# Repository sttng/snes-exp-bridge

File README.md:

# snes-exp-bridge
This project is intended to create a bridge board interface to the SNES expansion port broken out to DB-25 and 3.5mm barrel audio. The expansion port requires a costly proprietary connector from SAMTEC MEC2-30-01-L-DV or MEC2-50-01-L-TH1-WT or MEC2-50-01-L-DV. Some details also here: https://www.qwertymodo.com/hardware-projects/snes/snes-expansion-port-connector

The idea is instead of creating projects which source this connector, all downstream projects can now instead mate with the DB-25 connector which is cheaper and easier for interfacing. There are no active electrical components for this board. This repo contains altium design files and also newer KiCad files of the schematic/layout, photos and pdf docs.

Enjoy!
Evan

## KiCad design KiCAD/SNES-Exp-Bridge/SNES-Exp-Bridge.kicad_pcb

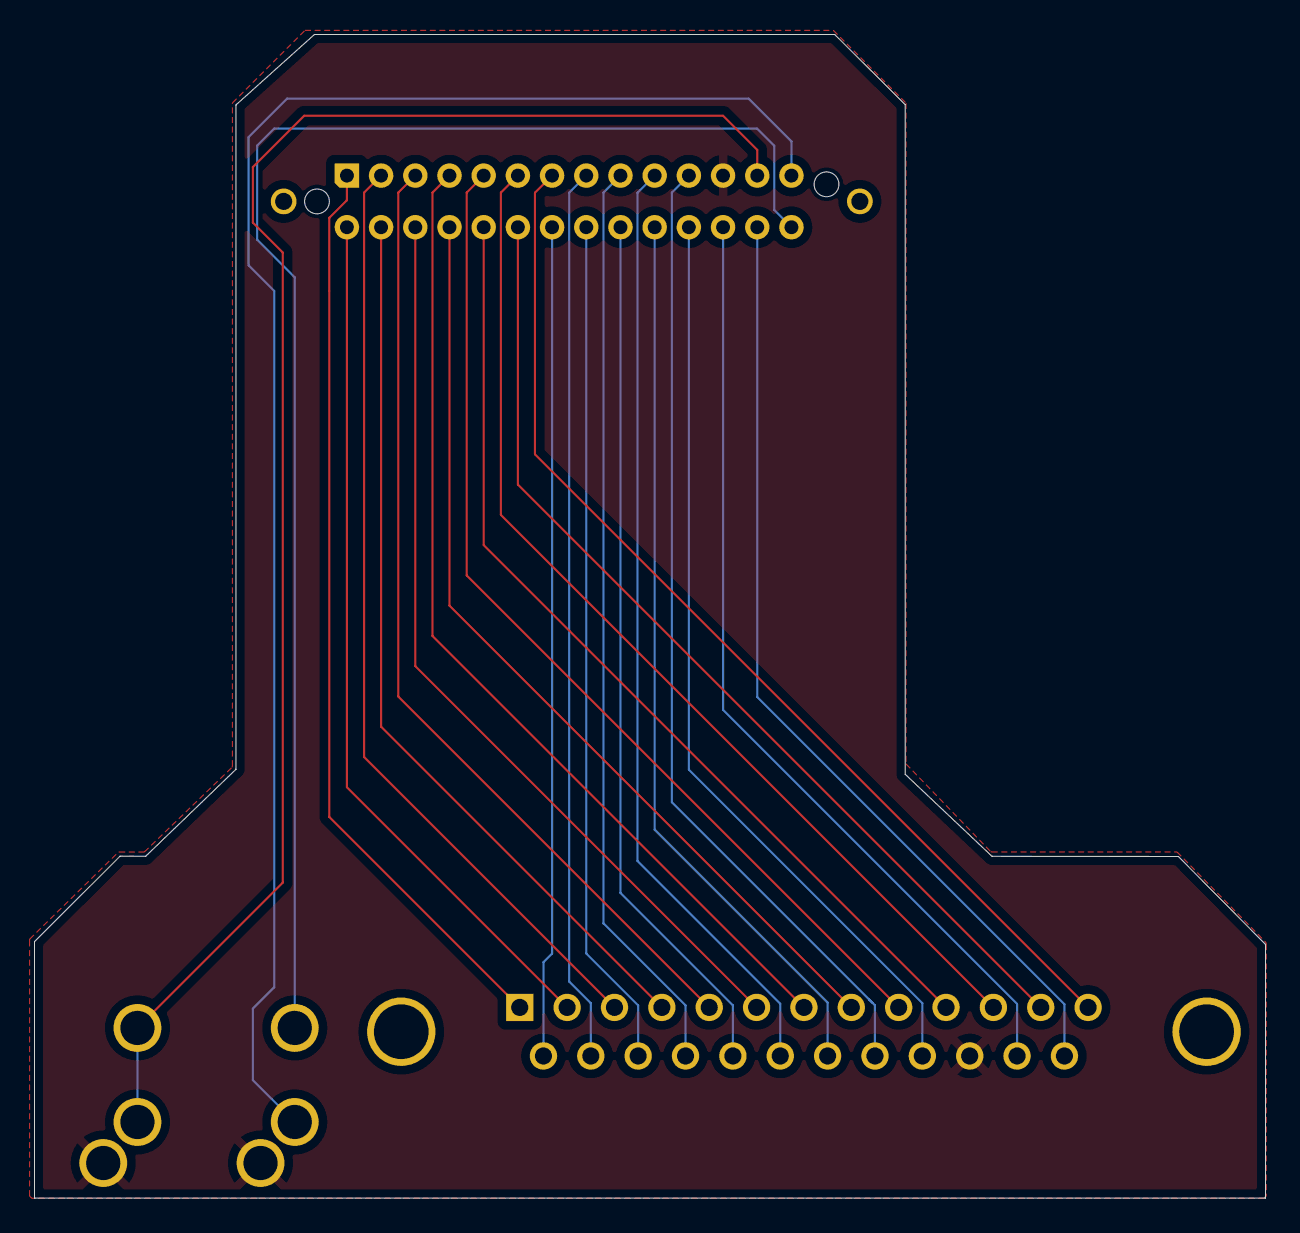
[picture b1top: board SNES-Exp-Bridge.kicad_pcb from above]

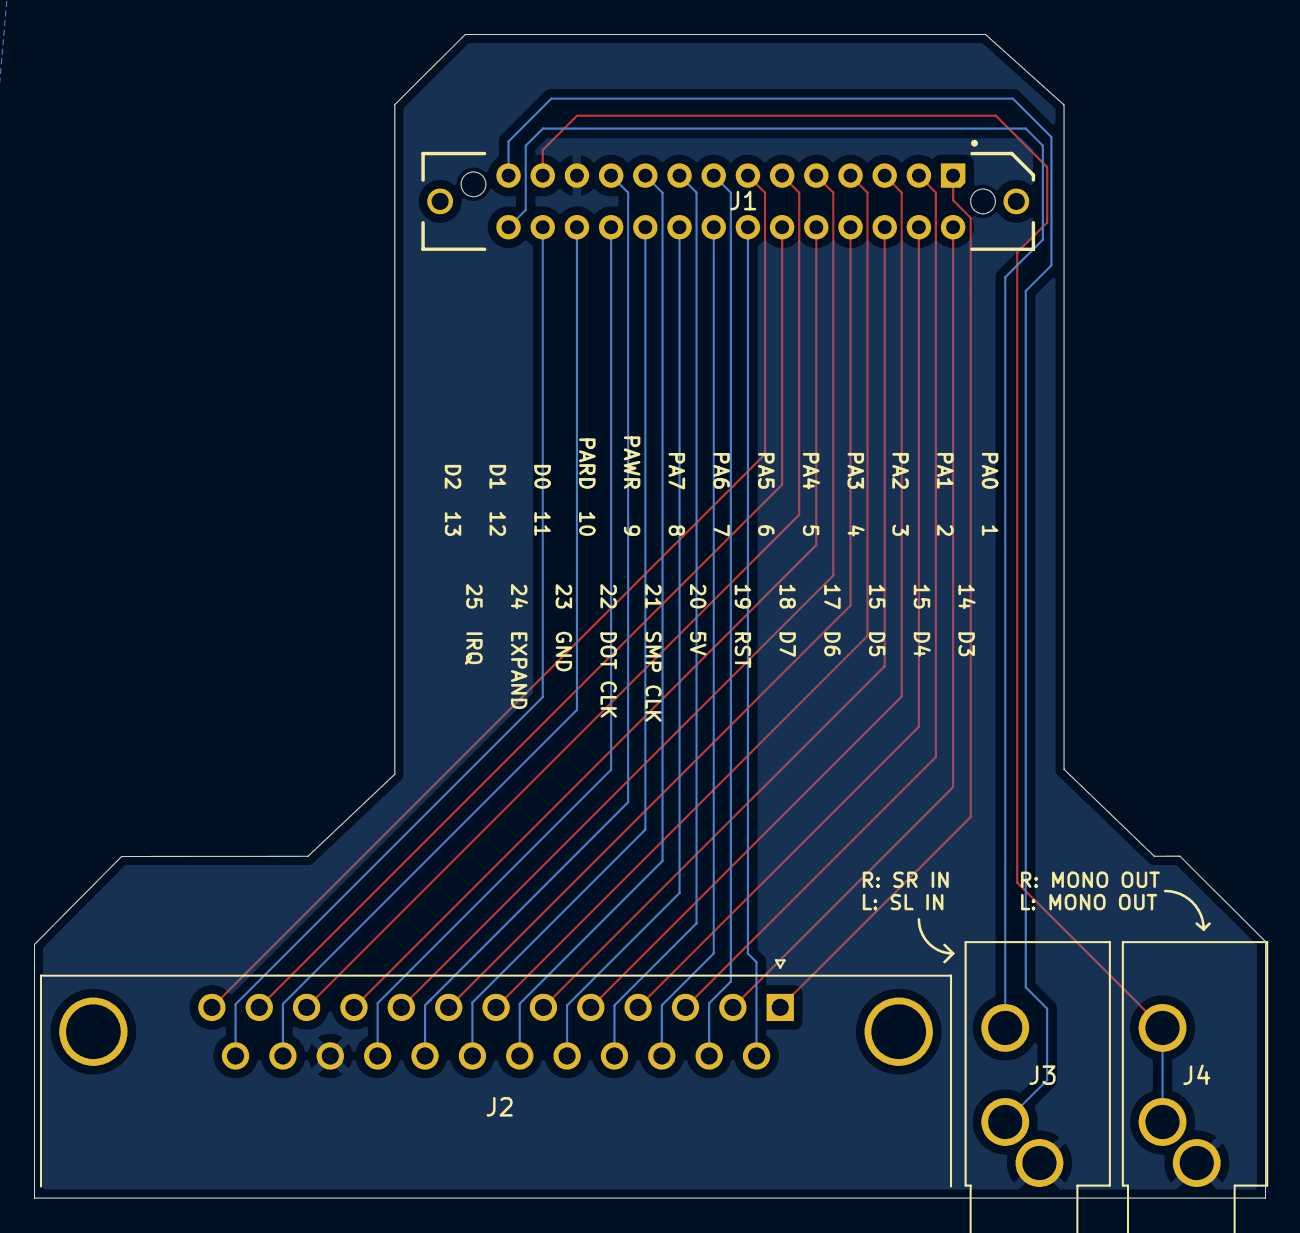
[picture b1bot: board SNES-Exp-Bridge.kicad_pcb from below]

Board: 4 copper layers, 72.0 x 68.0 mm, 4 parts (4 on the bottom side), 28 nets.

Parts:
J1: Conn_02x14_Odd_Even_MountingPin; SAMTEC_MEC2-50-01-X-TH1-WT
J2: DB25_Socket_MountingHoles; DSUB-25_Socket_Horizontal_P2.77x2.84mm_EdgePinOffset7.70mm_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
J3, J4: AudioJack3_Ground; Jack_3.5mm_CUI_SJ1-3533NG_Horizontal_CircularHoles

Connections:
+5V: J1.20, J2.20
/D0: J1.11, J2.11
/D1: J1.12, J2.12
/D2: J1.13, J2.13
/D3: J1.14, J2.14
/D4: J1.15, J2.15
/D5: J1.16, J2.16
/D6: J1.17, J2.17
/D7: J1.18, J2.18
/DOT_CLK: J1.22, J2.22
/EXPAND: J1.24, J2.24
/IRQ_n: J1.26, J2.25
/MONO_OUT: J1.25, J4.R, J4.T
/PA0: J1.1, J2.1
/PA1: J1.2, J2.2
/PA2: J1.3, J2.3
/PA3: J1.4, J2.4
/PA4: J1.5, J2.5
/PA5: J1.6, J2.6
/PA6: J1.7, J2.7
/PA7: J1.8, J2.8
/PARD: J1.10, J2.10
/PAWR: J1.9, J2.9
/SL_IN: J1.27, J3.T
/SMP_CLK: J1.21, J2.21
/SR_IN: J1.28, J3.R
/rst_n: J1.19, J2.19
GND: J1.23, J2.23, J3.S, J4.S
